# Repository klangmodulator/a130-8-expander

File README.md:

# a130-8-expander
Expander for the Doepfer A130-8 octal linear VCA eurorack module.
Link to Modwiggler thread: [https://modwiggler.com/forum/viewtopic.php?t=268533](https://modwiggler.com/forum/viewtopic.php?t=268533)

## Release 2024-10-12

### Added
- Initial commit PCB v2, revision A

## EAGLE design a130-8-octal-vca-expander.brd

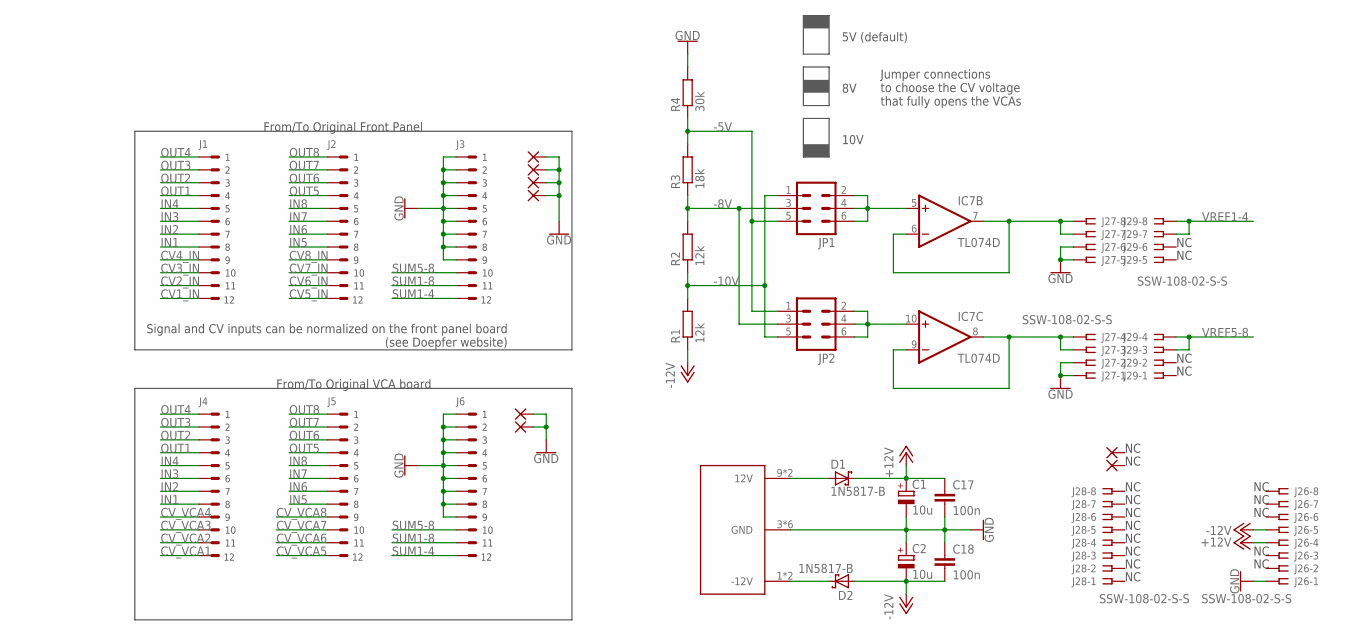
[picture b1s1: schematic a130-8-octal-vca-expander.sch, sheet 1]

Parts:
C1, C2: 10u; E2-5
C17, C18: 100n; C0603
D1, D2: 1N5817-B; DO41-7.6
IC7: TL074D; SO14
J1, J2, J3, J4, J5, J6: PIN_HEADER_1X12_2MM_GRID
J25: A100-BUS_HEADER_10P; DOEPFER_2X05
J26, J27, J28, J29: SSW-108-02-S-S
JP1, JP2: MA03-2
PAD1, PAD2, PAD3, PAD4, PAD5, PAD6, PAD7, PAD9: 2,15/1,0
R1, R2: 12k; M0805
R3: 18k; M0805
R4: 30k; M0805

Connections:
+12V: C1.+, C17.1, D1.C, J26.4; also elsewhere on the board
-5V: JP1.5, JP2.1, R3.2, R4.1
-8V: JP1.3, JP2.3, R2.2, R3.1
-10V: JP1.1, JP2.5, R1.2, R2.1
-12V: C2.-, C18.2, D2.A, J26.5, R1.1; also elsewhere on the board
CV1_IN: J1.12 (S11); also elsewhere on the board
CV2_IN: J1.11 (S10); also elsewhere on the board
CV3_IN: J1.10 (S9); also elsewhere on the board
CV4_IN: J1.9 (S8); also elsewhere on the board
CV5_IN: J2.12 (S11); also elsewhere on the board
CV6_IN: J2.11 (S10); also elsewhere on the board
CV7_IN: J2.10 (S9); also elsewhere on the board
CV8_IN: J2.9 (S8); also elsewhere on the board
CV_VCA1: J4.12 (S11); also elsewhere on the board
CV_VCA2: J4.11 (S10); also elsewhere on the board
CV_VCA3: J4.10 (S9); also elsewhere on the board
CV_VCA4: J4.9 (S8); also elsewhere on the board
CV_VCA5: J5.12 (S11); also elsewhere on the board
CV_VCA6: J5.11 (S10); also elsewhere on the board
CV_VCA7: J5.10 (S9); also elsewhere on the board
CV_VCA8: J5.9 (S8); also elsewhere on the board
GND: C1.-, C2.+, C17.2, C18.1, J3.1 (S1), J3.2 (S2), J3.3 (S3), J3.4 (S4), J3.5 (S), J3.6 (S5), J3.7 (S6), J3.8 (S7), J3.9 (S8), J6.1 (S1), J6.2 (S2), J6.3 (S3), J6.4 (S4), J6.5 (S), J6.6 (S5), J6.7 (S6), J6.8 (S7), J6.9 (S8), J25.3 (GND), J25.4 (GND), J25.5 (GND), J25.6 (GND), J25.7 (GND), J25.8 (GND), J26.1, J27.1, J27.2, J27.5, J27.6, PAD1.1, PAD2.1, PAD3.1, PAD4.1, PAD5.1, PAD6.1, R4.2; also elsewhere on the board
IN1: J1.8 (S7), J4.8 (S7)
IN2: J1.7 (S6), J4.7 (S6)
IN3: J1.6 (S5), J4.6 (S5)
IN4: J1.4 (S4), J4.4 (S4)
IN5: J2.8 (S7), J5.8 (S7)
IN6: J2.7 (S6), J5.7 (S6)
IN7: J2.6 (S5), J5.6 (S5)
IN8: J2.4 (S4), J5.4 (S4)
unnamed: D1.A, J25.9 (12V), J25.10 (12V)
unnamed: D2.C, J25.1 (-12V), J25.2 (-12V)
unnamed: IC7.5 (+IN), JP1.2, JP1.4, JP1.6
unnamed: IC7.6 (-IN), IC7.7 (OUT), J27.7, J27.8
unnamed: IC7.10 (+IN), JP2.2, JP2.4, JP2.6
unnamed: IC7.8 (OUT), IC7.9 (-IN), J27.3, J27.4
OUT1: J1.3 (S3), J4.3 (S3)
OUT2: J1.2 (S2), J4.2 (S2)
OUT3: J1.1 (S1), J4.1 (S1)
OUT4: J1.5 (S), J4.5 (S)
OUT5: J2.3 (S3), J5.3 (S3)
OUT6: J2.2 (S2), J5.2 (S2)
OUT7: J2.1 (S1), J5.1 (S1)
OUT8: J2.5 (S), J5.5 (S)
SUM1-4: J3.12 (S11), J6.12 (S11)
SUM1-8: J3.11 (S10), J6.11 (S10)
SUM5-8: J3.10 (S9), J6.10 (S9)
VREF1-4: J29.7, J29.8; also elsewhere on the board
VREF5-8: J29.3, J29.4; also elsewhere on the board

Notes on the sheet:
From/To Original Front Panel
Jumper connections to choose the CV voltage that fully opens the VCAs
5V (default)
10V
From/To Original VCA board
Signal and CV inputs can be normalized on the front panel board (see Doepfer website)

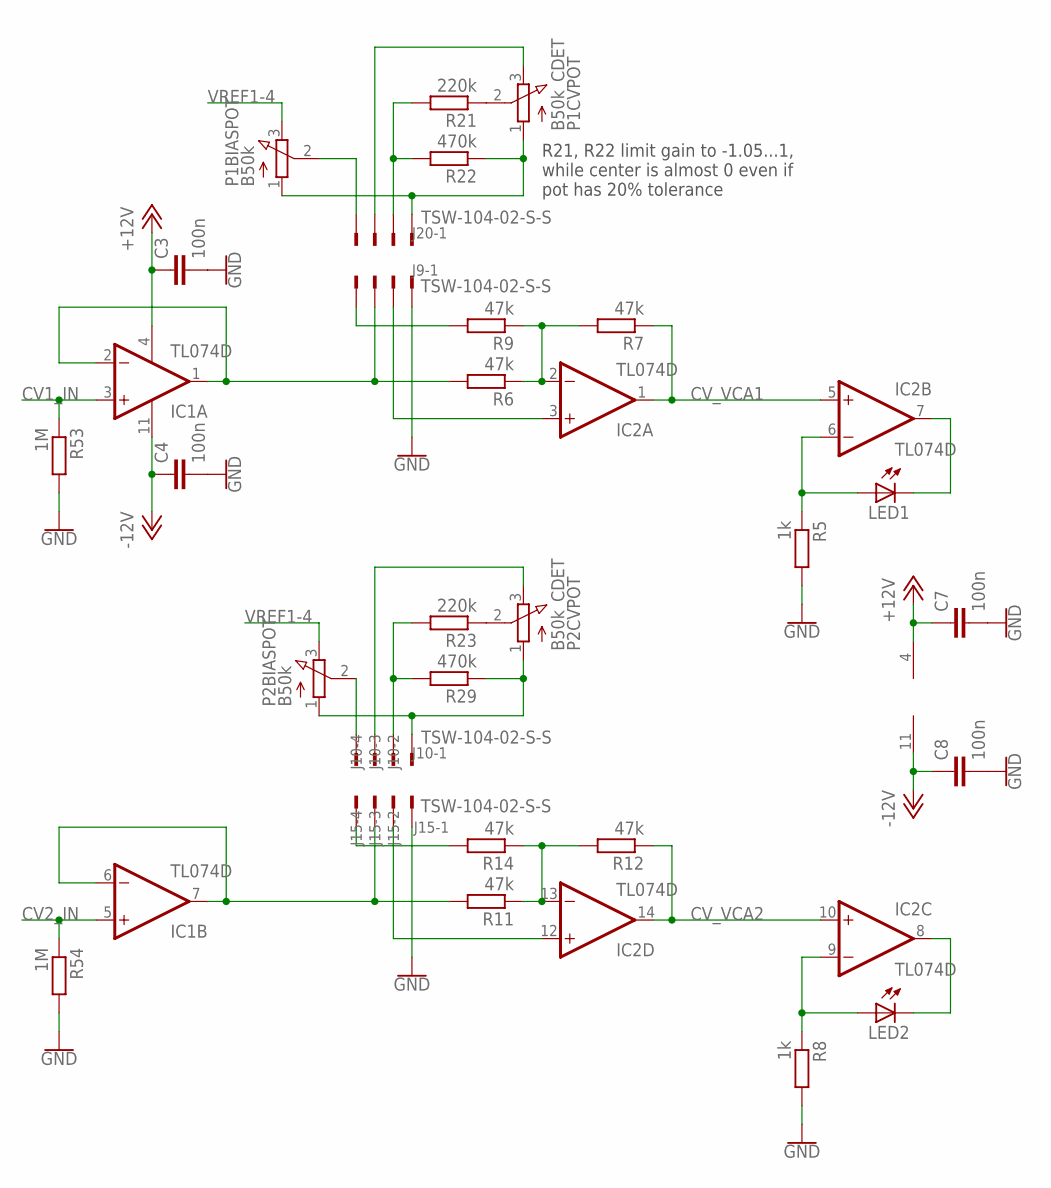
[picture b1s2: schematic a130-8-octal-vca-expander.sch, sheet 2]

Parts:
C3, C4, C7, C8: 100n; C0603
IC1, IC2, IC3: TL074D; SO14
J9, J10, J15, J20: TSW-104-02-S-S
LED1, LED2: LED3MM
P1BIAS, P2BIAS: B50k; EVUF
P1CV, P2CV: B50k_CDET; EVUF
R5, R8: 1k; M0805
R6, R7, R9, R11, R12, R14: 47k; M0805
R21, R23: 220k; M0805
R22, R29: 470k; M0805
R53, R54: 1M; M0805

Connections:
+12V: C3.1, C7.1, IC1.4 (V+), IC3.4 (V+); also elsewhere on the board
-12V: C4.1, C8.1, IC1.11 (V-), IC3.11 (V-); also elsewhere on the board
CV1_IN: IC1.3 (+IN), R53.1; also elsewhere on the board
CV2_IN: IC1.5 (+IN), R54.1; also elsewhere on the board
CV_VCA1: IC2.1 (OUT), IC2.5 (+IN), R7.1; also elsewhere on the board
CV_VCA2: IC2.10 (+IN), IC2.14 (OUT), R12.1; also elsewhere on the board
GND: C3.2, C4.2, C7.2, C8.2, J15.1, J20.1, R5.2, R8.2, R53.2, R54.2; also elsewhere on the board
unnamed: J9.4, P1BIAS.2
unnamed: IC1.1 (OUT), IC1.2 (-IN), J20.3, R6.2
unnamed: IC2.2 (-IN), R6.1, R7.2, R9.1
unnamed: J20.4, R9.2
unnamed: IC1.6 (-IN), IC1.7 (OUT), J15.3, R11.2
unnamed: IC2.12 (+IN), J15.2
unnamed: IC2.13 (-IN), R11.1, R12.2, R14.1
unnamed: J9.1, P1BIAS.1, P1CV.1, R22.1
unnamed: IC2.6 (-IN), LED1.A, R5.1
unnamed: IC2.7 (OUT), LED1.K (C)
unnamed: IC2.8 (OUT), LED2.K (C)
unnamed: IC2.9 (-IN), LED2.A, R8.1
unnamed: J15.4, R14.2
unnamed: P2CV.2, R23.1
unnamed: J9.3, P1CV.3
unnamed: IC2.3 (+IN), J20.2
unnamed: J10.1, P2BIAS.1, P2CV.1, R29.1
unnamed: J10.2, R23.2, R29.2
unnamed: J10.3, P2CV.3
unnamed: J10.4, P2BIAS.2
unnamed: P1CV.2, R21.1
unnamed: J9.2, R21.2, R22.2
VREF1-4: P1BIAS.3, P2BIAS.3; also elsewhere on the board

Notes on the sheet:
R21, R22 limit gain to -1.05...1, while center is almost 0 even if pot has 20% tolerance

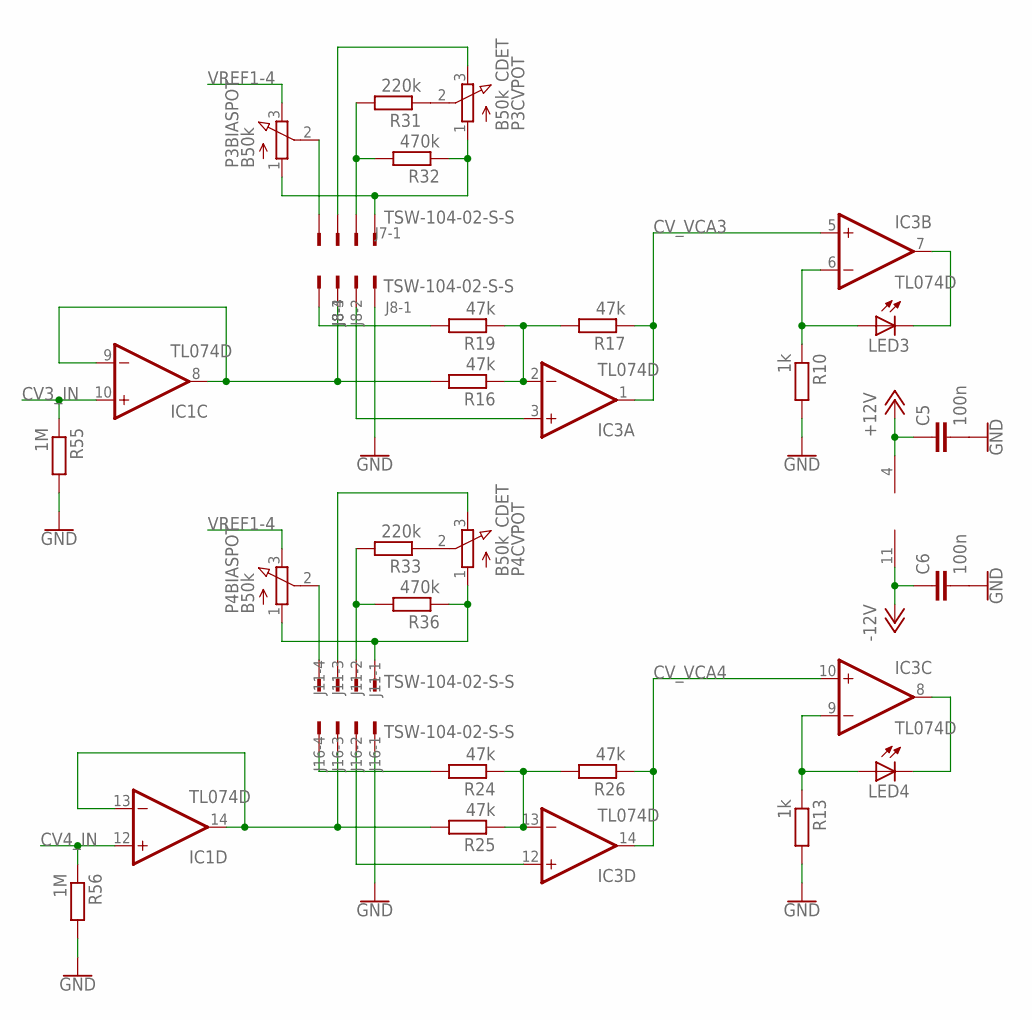
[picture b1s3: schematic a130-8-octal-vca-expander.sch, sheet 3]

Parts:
C5, C6: 100n; C0603
IC1, IC2, IC3: TL074D; SO14
J7, J8, J11, J16: TSW-104-02-S-S
LED3, LED4: LED3MM
P3BIAS, P4BIAS: B50k; EVUF
P3CV, P4CV: B50k_CDET; EVUF
R10, R13: 1k; M0805
R16, R17, R19, R24, R25, R26: 47k; M0805
R31, R33: 220k; M0805
R32, R36: 470k; M0805
R55, R56: 1M; M0805

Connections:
+12V: C5.1, IC2.4 (V+); also elsewhere on the board
-12V: C6.1, IC2.11 (V-); also elsewhere on the board
CV3_IN: IC1.10 (+IN), R55.1; also elsewhere on the board
CV4_IN: IC1.12 (+IN), R56.1; also elsewhere on the board
CV_VCA3: IC3.1 (OUT), IC3.5 (+IN), R17.1; also elsewhere on the board
CV_VCA4: IC3.10 (+IN), IC3.14 (OUT), R26.1; also elsewhere on the board
GND: C5.2, C6.2, J8.1, J16.1, R10.2, R13.2, R55.2, R56.2; also elsewhere on the board
unnamed: IC1.8 (OUT), IC1.9 (-IN), J8.3, R16.2
unnamed: J7.4, P3BIAS.2
unnamed: IC3.2 (-IN), R16.1, R17.2, R19.1
unnamed: J8.4, R19.2
unnamed: IC1.13 (-IN), IC1.14 (OUT), J16.3, R25.2
unnamed: J16.4, R24.2
unnamed: IC3.13 (-IN), R24.1, R25.1, R26.2
unnamed: IC3.12 (+IN), J16.2
unnamed: IC3.6 (-IN), LED3.A, R10.1
unnamed: IC3.7 (OUT), LED3.K (C)
unnamed: IC3.9 (-IN), LED4.A, R13.1
unnamed: IC3.8 (OUT), LED4.K (C)
unnamed: J7.1, P3BIAS.1, P3CV.1, R32.1
unnamed: J7.2, R31.2, R32.2
unnamed: J7.3, P3CV.3
unnamed: IC3.3 (+IN), J8.2
unnamed: J11.1, P4BIAS.1, P4CV.1, R36.1
unnamed: J11.4, P4BIAS.2
unnamed: J11.3, P4CV.3
unnamed: J11.2, R33.2, R36.2
unnamed: P3CV.2, R31.1
unnamed: P4CV.2, R33.1
VREF1-4: P3BIAS.3, P4BIAS.3; also elsewhere on the board

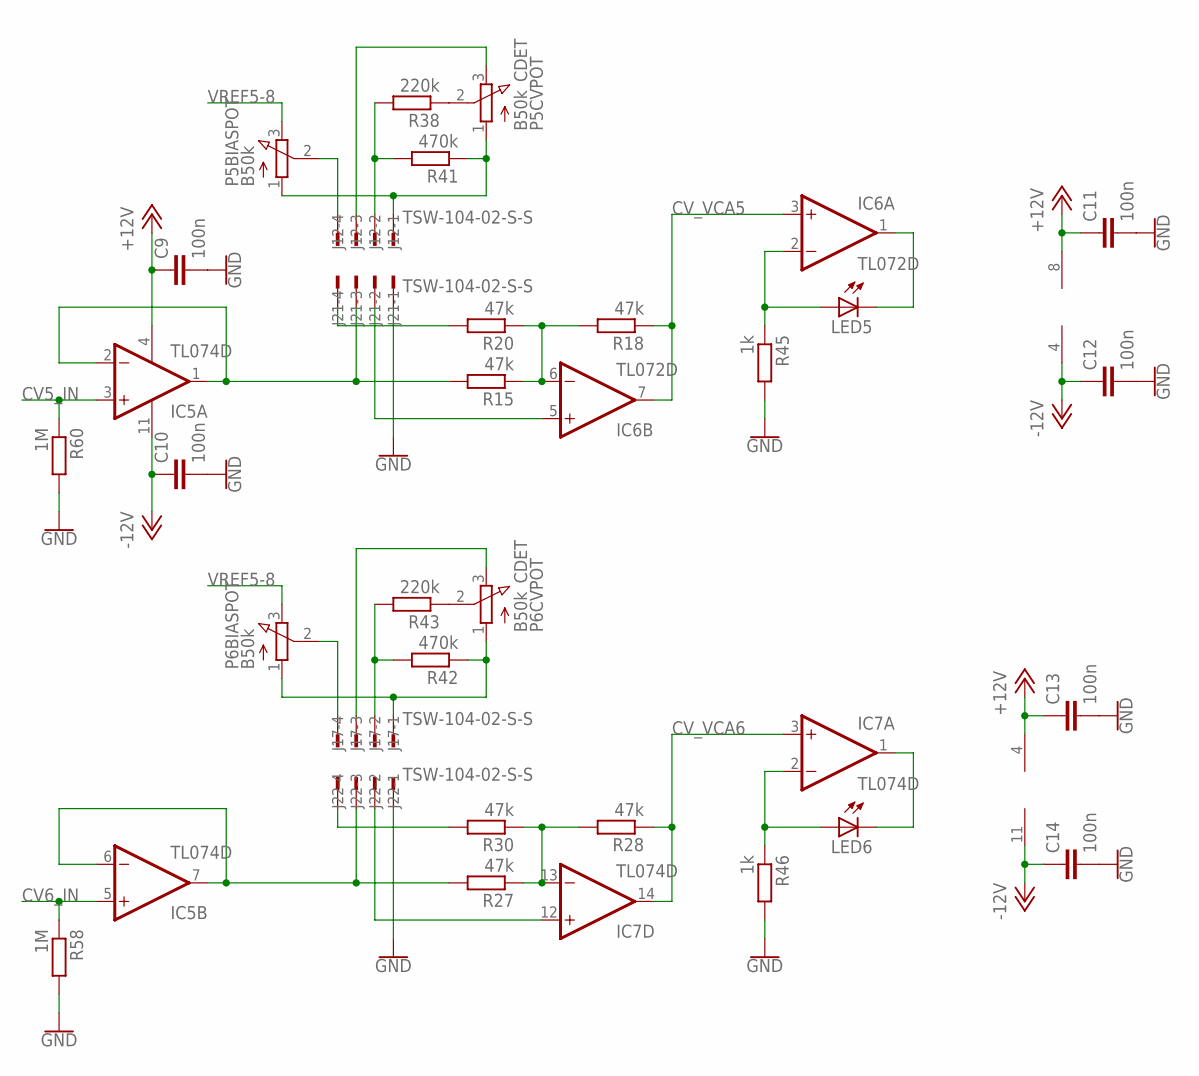
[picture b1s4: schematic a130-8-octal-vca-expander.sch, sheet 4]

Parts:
C9, C10, C11, C12, C13, C14: 100n; C0603
IC5, IC7: TL074D; SO14
IC6: TL072D; SO08
J12, J17, J21, J22: TSW-104-02-S-S
LED5, LED6: LED3MM
P5BIAS, P6BIAS: B50k; EVUF
P5CV, P6CV: B50k_CDET; EVUF
R15, R18, R20, R27, R28, R30: 47k; M0805
R38, R43: 220k; M0805
R41, R42: 470k; M0805
R45, R46: 1k; M0805
R58, R60: 1M; M0805

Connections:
+12V: C9.1, C11.1, C13.1, IC5.4 (V+), IC6.8 (V+), IC7.4 (V+); also elsewhere on the board
-12V: C10.1, C12.1, C14.1, IC5.11 (V-), IC6.4 (V-), IC7.11 (V-); also elsewhere on the board
CV5_IN: IC5.3 (+IN), R60.1; also elsewhere on the board
CV6_IN: IC5.5 (+IN), R58.1; also elsewhere on the board
CV_VCA5: IC6.3 (+IN), IC6.7 (OUT), R18.1; also elsewhere on the board
CV_VCA6: IC7.3 (+IN), IC7.14 (OUT), R28.1; also elsewhere on the board
GND: C9.2, C10.2, C11.2, C12.2, C13.2, C14.2, J21.1, J22.1, R45.2, R46.2, R58.2, R60.2; also elsewhere on the board
unnamed: J17.4, P6BIAS.2
unnamed: IC5.1 (OUT), IC5.2 (-IN), J21.3, R15.2
unnamed: J12.2, R38.2, R41.2
unnamed: IC6.6 (-IN), R15.1, R18.2, R20.1
unnamed: J12.1, P5BIAS.1, P5CV.1, R41.1
unnamed: IC5.6 (-IN), IC5.7 (OUT), J22.3, R27.2
unnamed: J17.1, P6BIAS.1, P6CV.1, R42.1
unnamed: IC7.13 (-IN), R27.1, R28.2, R30.1
unnamed: J22.4, R30.2
unnamed: IC6.2 (-IN), LED5.A, R45.1
unnamed: IC6.1 (OUT), LED5.K (C)
unnamed: IC7.1 (OUT), LED6.K (C)
unnamed: IC7.2 (-IN), LED6.A, R46.1
unnamed: J17.2, R42.2, R43.2
unnamed: J12.3, P5CV.3
unnamed: J12.4, P5BIAS.2
unnamed: IC6.5 (+IN), J21.2
unnamed: J21.4, R20.2
unnamed: J17.3, P6CV.3
unnamed: IC7.12 (+IN), J22.2
unnamed: P5CV.2, R38.1
unnamed: P6CV.2, R43.1
VREF5-8: P5BIAS.3, P6BIAS.3; also elsewhere on the board

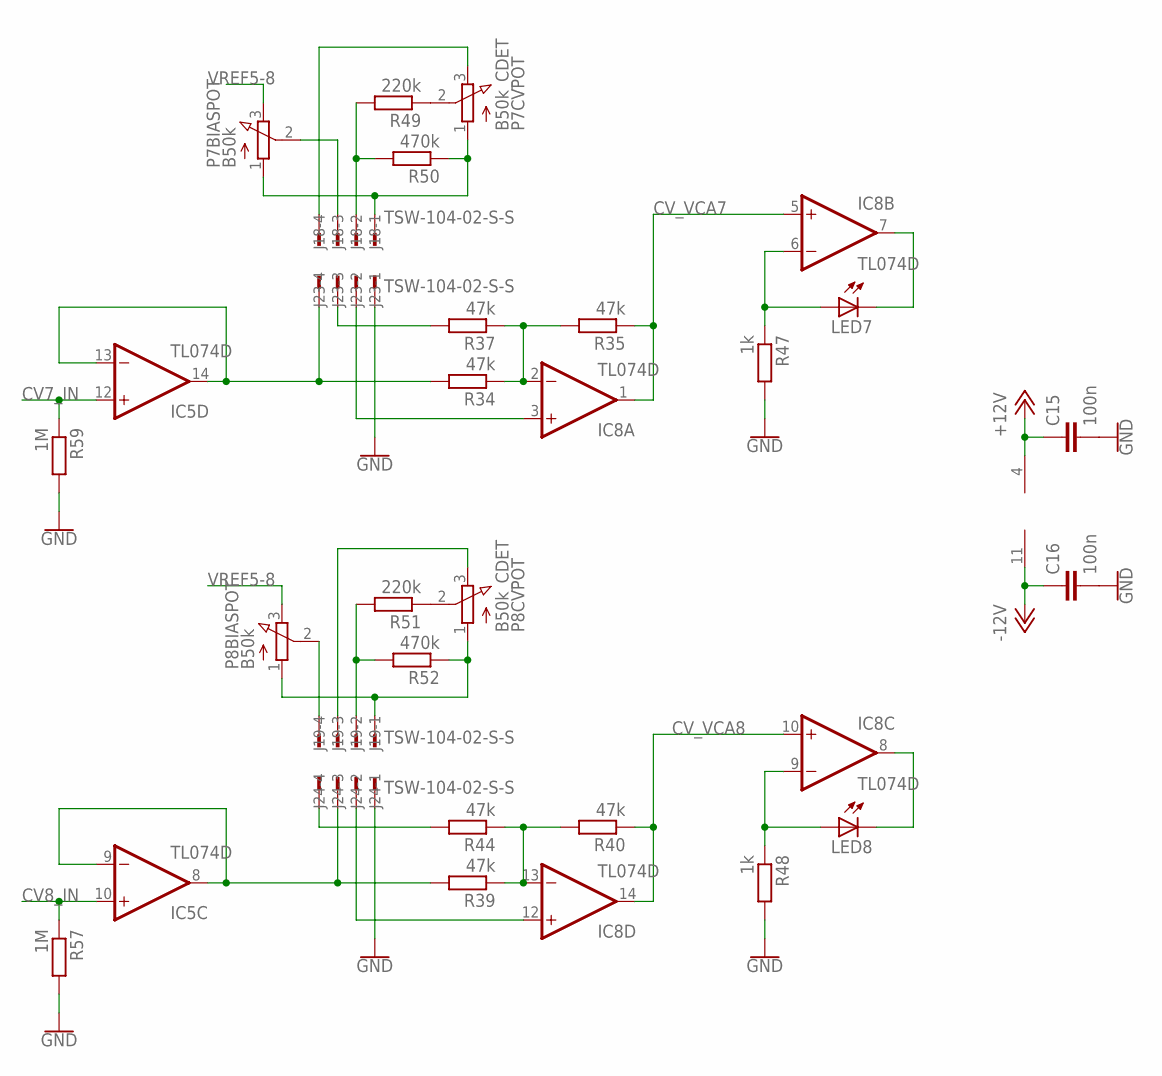
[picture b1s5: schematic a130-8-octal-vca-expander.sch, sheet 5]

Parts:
C15, C16: 100n; C0603
IC5, IC8: TL074D; SO14
J18, J19, J23, J24: TSW-104-02-S-S
LED7, LED8: LED3MM
P7BIAS, P8BIAS: B50k; EVUF
P7CV, P8CV: B50k_CDET; EVUF
R34, R35, R37, R39, R40, R44: 47k; M0805
R47, R48: 1k; M0805
R49, R51: 220k; M0805
R50, R52: 470k; M0805
R57, R59: 1M; M0805

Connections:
+12V: C15.1, IC8.4 (V+); also elsewhere on the board
-12V: C16.1, IC8.11 (V-); also elsewhere on the board
CV7_IN: IC5.12 (+IN), R59.1; also elsewhere on the board
CV8_IN: IC5.10 (+IN), R57.1; also elsewhere on the board
CV_VCA7: IC8.1 (OUT), IC8.5 (+IN), R35.1; also elsewhere on the board
CV_VCA8: IC8.10 (+IN), IC8.14 (OUT), R40.1; also elsewhere on the board
GND: C15.2, C16.2, J23.1, J24.1, R47.2, R48.2, R57.2, R59.2; also elsewhere on the board
unnamed: J23.3, R37.2
unnamed: J18.4, P7CV.3
unnamed: IC8.2 (-IN), R34.1, R35.2, R37.1
unnamed: J18.2, R49.2, R50.2
unnamed: IC5.8 (OUT), IC5.9 (-IN), J24.3, R39.2
unnamed: J19.1, P8BIAS.1, P8CV.1, R52.1
unnamed: IC8.13 (-IN), R39.1, R40.2, R44.1
unnamed: IC8.12 (+IN), J24.2
unnamed: IC8.6 (-IN), LED7.A, R47.1
unnamed: IC8.7 (OUT), LED7.K (C)
unnamed: IC8.9 (-IN), LED8.A, R48.1
unnamed: IC8.8 (OUT), LED8.K (C)
unnamed: P7CV.2, R49.1
unnamed: J18.1, P7BIAS.1, P7CV.1, R50.1
unnamed: IC5.13 (-IN), IC5.14 (OUT), J23.4, R34.2
unnamed: J18.3, P7BIAS.2
unnamed: J19.3, P8CV.3
unnamed: IC8.3 (+IN), J23.2
unnamed: J19.4, P8BIAS.2
unnamed: J24.4, R44.2
unnamed: P8CV.2, R51.1
unnamed: J19.2, R51.2, R52.2
VREF5-8: P7BIAS.3, P8BIAS.3; also elsewhere on the board

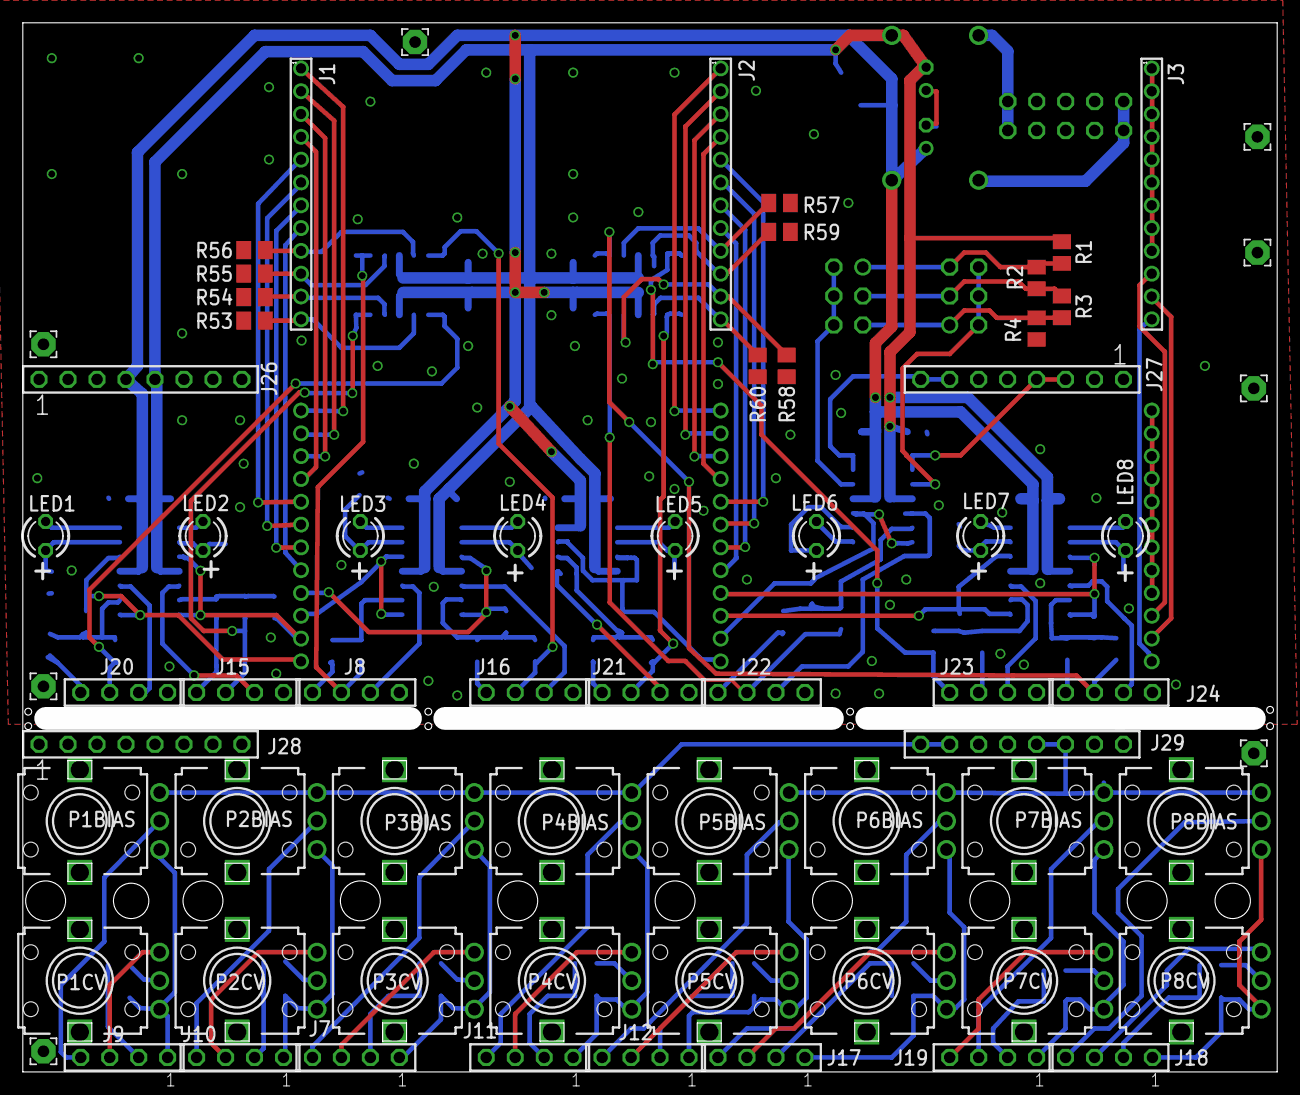
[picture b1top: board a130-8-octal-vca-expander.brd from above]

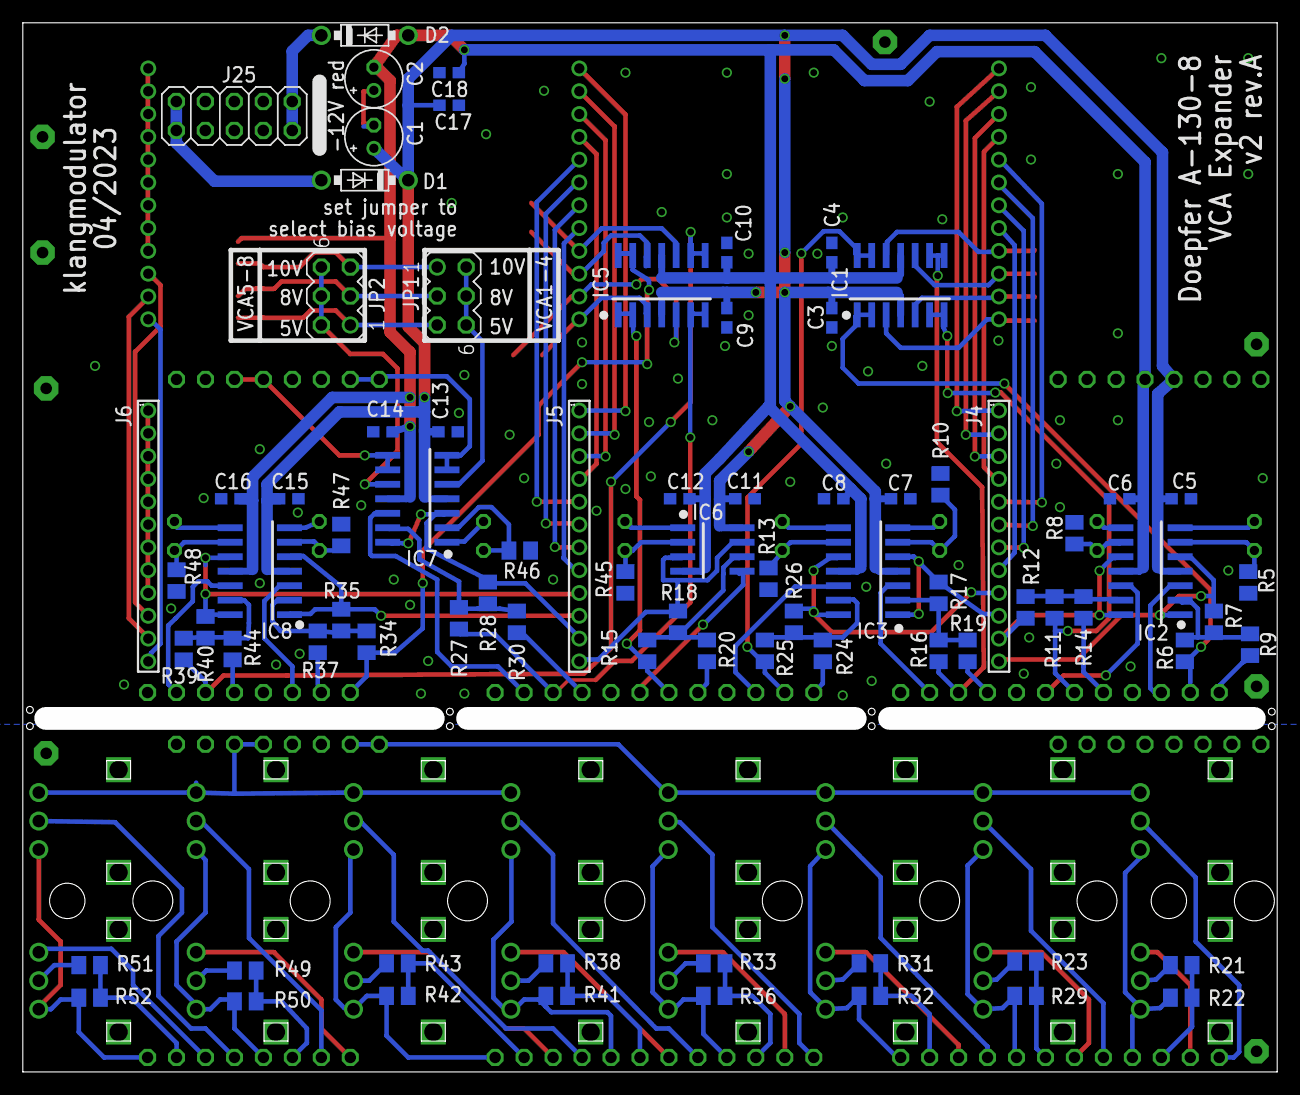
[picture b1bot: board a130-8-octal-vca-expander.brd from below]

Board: 2 copper layers, 108.0 x 90.0 mm, 148 parts (81 on the bottom side), 137 nets.

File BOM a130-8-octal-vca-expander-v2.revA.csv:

Qty,Value,Parts,Mouser Link
8,Bicolor LED red/green 3 mm through hole,"LED1, LED2, LED3, LED4, LED5, LED6, LED7, LED8",859-LTL-14CHJ
2,PIN HEADER MALE 2x3 2.54 mm grid,"JP1, JP2",
3,M22-7131242,"J1, J2, J3",855-M22-7131242
3,M22-2511205,"J4, J5, J6",855-M22-2511205
16,100n,"C3, C4, C5, C6, C7, C8, C9, C10, C11, C12, C13, C14, C15, C16, C17, C18",CL10B104KA8NFNC 
2,10u,"C1, C2",710-860240572001
2,12k,"R1, R2",652-CR0805FX-1202ELF
1,18k,R3,652-CR0805FX-1802ELF
8,1M,"R53, R54, R55, R56, R57, R58, R59, R60",652-CR0805FX-1004ELF
2,1N5817-B,"D1, D2",750-1N5817T-G
8,1k,"R5, R8, R10, R13, R45, R46, R47, R48",652-CR0805FX-1001ELF
8,220k,"R21, R23, R31, R33, R38, R43, R49, R51",652-CR0805FX-2203ELF
1,30k,R4,652-CR0805FX-3002ELF
8,470k,"R22, R29, R32, R36, R41, R42, R50, R52",652-CR0805FX-4703ELF
24,47k,"R6, R7, R9, R11, R12, R14, R15, R16, R17, R18, R19, R20, R24, R25, R26, R27, R28, R30, R34, R35, R37, R39, R40, R44",652-CR0805FX-4702ELF
1,PIN HEADER MALE 2x5 2.54 mm grid,J25,
8,B50k,"P1BIAS, P2BIAS, P3BIAS, P4BIAS, P5BIAS, P6BIAS, P7BIAS, P8BIAS","https://www.thonk.co.uk/shop/ttpots/ 9 mm potentiometer TT electronics vertical PCB mount, 6 mm shaft"
8,B50k_CDET,"P1CV, P2CV, P3CV, P4CV, P5CV, P6CV, P7CV, P8CV","https://www.thonk.co.uk/shop/ttpots/ 9 mm potentiometer TT electronics vertical PCB mount, 6 mm shaft, center detent"
3,PIN HEADER MALE 1x8 2.54 mm grid,"J18, J19, J28, J29",
3,PIN HEADER FEMALE 1x8 2.54 mm grid,"J23, J24, J26, J27",
1,TL072D,IC6,595-TL072CDR
6,TL074D,"IC1, IC2, IC3, IC5, IC7, IC8",595-TL074CDR
2,PIN HEADER MALE 1x12 2.54 mm grid,"J9, J10, J7, J11, J12, J19",
2,PIN HEADER FEMALE 1x12 2.54 mm grid,"J8, J15, J16, J20, J21, J22",

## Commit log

2024-10-13 Initial commit version v2 revision A
2024-10-13 Added link to modwiggler thread to readme
2024-10-13 Fixed missing trace on net N$58

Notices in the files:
parts and their libraries:
SparkFun-PowerSymbols: Licensing: Creative Commons ShareAlike 4.0 International - https://creativecommons.org/licenses/by-sa/4.0
